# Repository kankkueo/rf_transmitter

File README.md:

# RF transmitter

## Contributors

### [Elmo Kankkunen](https://github.com/kankkueo)

### [Miikka Mäki](https://github.com/mimimaki)

### [Visa Kurvi](https://github.com/visakurvi)

## Description

The project is very low power and thus legal, but be aware of your local laws and regulations!

RF transmitter project for Aalto university course Elektroniikkapaja. The transmitter consists of a digital and analog circuits. The digital circuit has an ATMEGA328 microcontroller, which controls a digital potentiometer. This potentiometer sets the voltage level of an MAX2606 VCO input. This is how the transmitter frequency is controlled. Audio from a microphone is then modulated to this FM-signal. 

## Screenshots

## SDR++ captured demo

[Demo video](https://drive.google.com/file/d/1DeKwweD5EkPlx5URQ9tuIAPdqHnWOvnQ/view?usp=sharing/)

## License

MIT License

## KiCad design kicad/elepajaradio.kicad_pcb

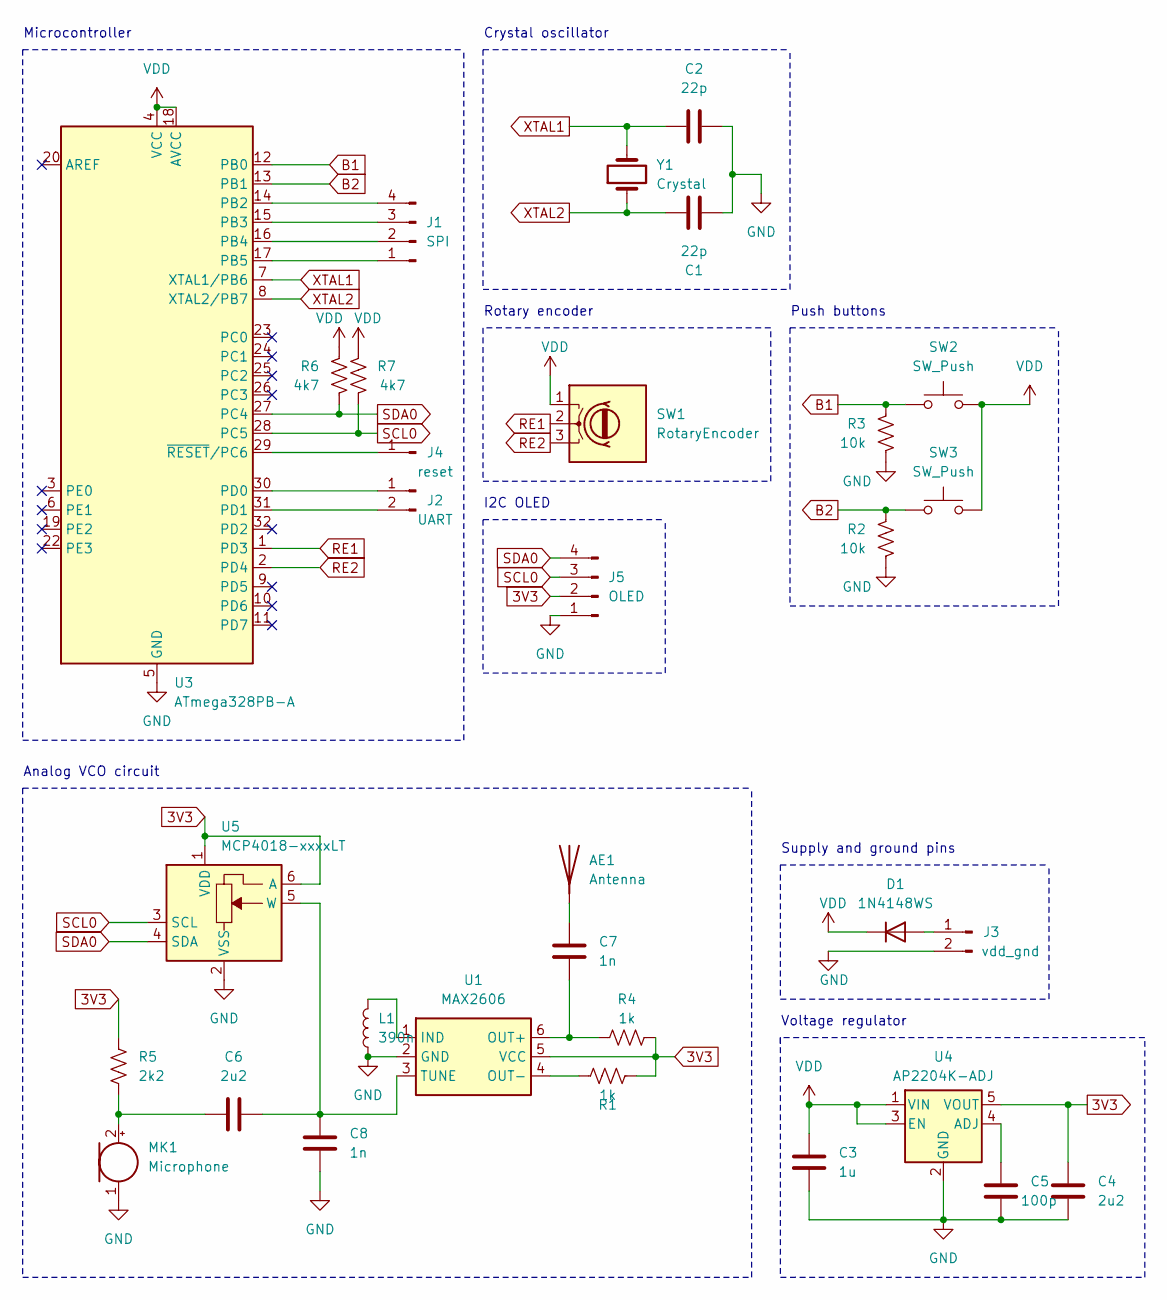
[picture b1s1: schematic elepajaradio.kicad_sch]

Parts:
AE1: Antenna; SMA_Amphenol_901-143_Horizontal
C1, C2: 22p; C_0603_1608Metric
C3: 1u; C_0603_1608Metric
C4, C6: 2u2; C_0603_1608Metric
C5: 100p; C_0603_1608Metric
C7, C8: 1n; C_0603_1608Metric
D1: 1N4148WS; D_SOD-323
J1: SPI; PinHeader_1x04_P2.54mm_Vertical
J2: UART; PinHeader_1x02_P2.54mm_Vertical
J3: vdd_gnd; PinHeader_1x02_P2.54mm_Vertical
J4: reset; PinHeader_1x01_P2.54mm_Vertical
J5: OLED; PinHeader_1x04_P2.54mm_Vertical
L1: 390n; L_0603_1608Metric
MK1: Microphone; PinHeader_1x02_P2.54mm_Vertical
R1, R4: 1k; R_0603_1608Metric
R2, R3: 10k; R_0603_1608Metric
R5: 2k2; R_0603_1608Metric
R6, R7: 4k7; R_0603_1608Metric
SW1: RotaryEncoder; PinHeader_1x03_P2.54mm_Vertical
SW2, SW3: SW_Push; PinHeader_1x02_P2.54mm_Vertical
U1: MAX2606; SOT-23-6
U3: ATmega328PB-A; TQFP-32_7x7mm_P0.8mm
U4: AP2204K-ADJ; SOT-23-5
U5: MCP4018-xxxxLT; SOT-363_SC-70-6
Y1: Crystal; Crystal_HC18-U_Vertical

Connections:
3V3: C4.1, J5.2, R1.1, R4.1, R5.2, U1.5 (VCC), U4.5 (VOUT), U5.1 (VDD), U5.6 (A)
B1: R3.2, SW2.1, U3.12 (PB0)
B2: R2.2, SW3.1, U3.13 (PB1)
GND: AE1.2, C1.2, C2.2, C3.2, C4.2, C5.2, C8.2, J3.2, J5.1, L1.1, MK1.1 (-), R2.1, R3.1, U1.2 (GND), U3.5 (GND), U3.21 (GND), U4.2 (GND), U5.2 (VSS)
unnamed: AE1.1 (A), C7.1
unnamed: D1.2 (A), J3.1
unnamed: J1.1, U3.17 (PB5)
unnamed: J1.2, U3.16 (PB4)
unnamed: J1.3, U3.15 (PB3)
unnamed: J1.4, U3.14 (PB2)
unnamed: J2.1, U3.30 (PD0)
unnamed: J2.2, U3.31 (PD1)
unnamed: J4.1, U3.29 (~RESET/PC6)
unnamed: C6.1, MK1.2 (+), R5.1
unnamed: L1.2, U1.1 (IND)
unnamed: C7.2, R4.2, U1.6 (OUT+)
unnamed: R1.2, U1.4 (OUT-)
unnamed: C6.2, C8.1, U1.3 (TUNE), U5.5 (W)
unnamed: C5.1, U4.4 (ADJ)
RE1: SW1.2, U3.1 (PD3)
RE2: SW1.3, U3.2 (PD4)
SCL0: J5.3, R7.1, U3.28 (PC5), U5.3 (SCL)
SDA0: J5.4, R6.1, U3.27 (PC4), U5.4 (SDA)
VDD: C3.1, D1.1 (K), R6.2, R7.2, SW1.1, SW2.2, SW3.2, U3.4 (VCC), U3.18 (AVCC), U4.1 (VIN), U4.3 (EN)
XTAL1: C2.1, U3.7 (XTAL1/PB6), Y1.2
XTAL2: C1.1, U3.8 (XTAL2/PB7), Y1.1

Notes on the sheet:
Microcontroller
Analog VCO circuit
Crystal oscillator
I2C OLED
Push buttons
Supply and ground pins
Rotary encoder
Voltage regulator

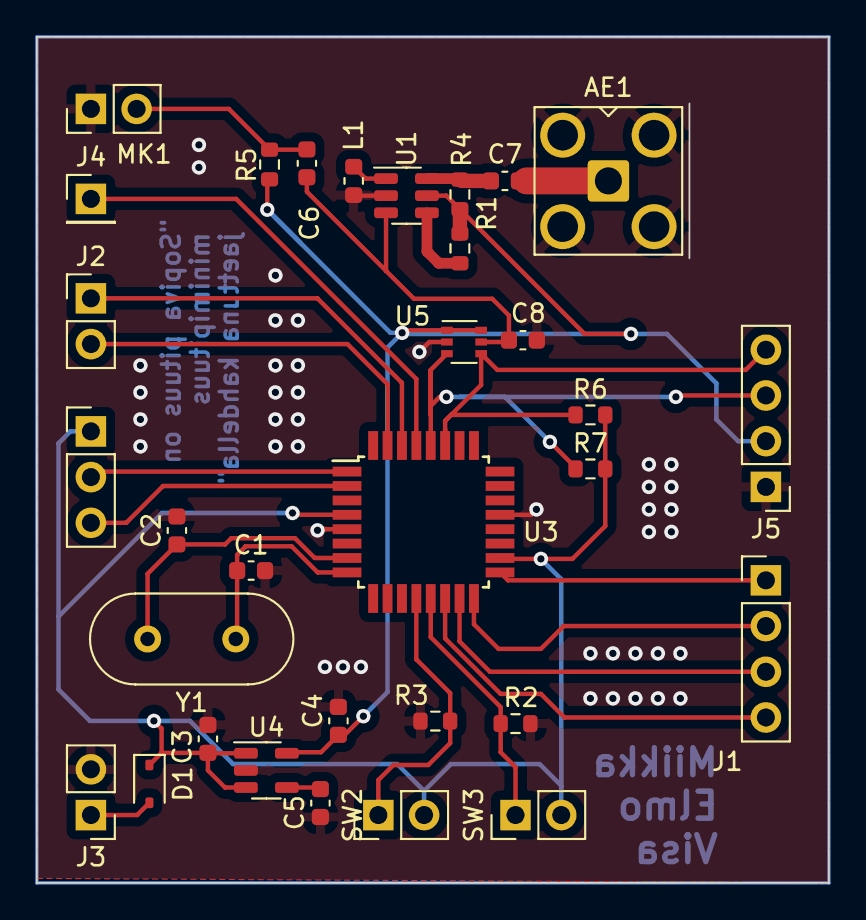
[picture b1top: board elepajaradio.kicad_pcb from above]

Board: 2 copper layers, 44.0 x 47.0 mm, 32 parts (0 on the bottom side), 26 nets.

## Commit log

2023-10-17 Add readme
2023-10-23 lisätään kicad projekti
2023-10-26 kicad update
2023-10-26 adding doc file and spice simulation file
2023-10-30 new circuit added
2023-11-07 initial pcb design and adding antenna connector
2023-11-09 resized transmission line for pcb
2023-11-09 sized transmission line v2
2023-11-09 adding PCB gbr and drl files
2023-11-24 initial C program
2023-11-25 fixes on new branch for 3v3 node
2023-11-26 fixing vco output nodes
2023-11-26 schematic updates for documentation
2023-11-28 makefile
2023-11-28 adding 3D model
2023-11-28 updates for second order
2023-11-28 Edited port values
2023-12-02 kicad gitignore
2023-12-04 removing unnecessary files
2023-12-04 making documentation in README
2023-12-04 figures for documentation
2023-12-04 fixing video extension
2023-12-04 fixing readme
2023-12-04 cleaning git
2023-12-07 combining i2cmaster.c and main.c
2023-12-08 edited main
2023-12-08 new i2c lib
2023-12-10 added temporary .ino testing code
2023-12-13 Working potentiometer
2023-12-13 deleted ino files
2023-12-13 deleted binary files
2023-12-14 Display frequency mapping
2023-12-14 Added software readme
2023-12-14 remoced old lib
2023-12-14 pull-up resistors and diode added
2023-12-14 fix readme this time maybe
2023-12-14 updating figures
2023-12-14 fixing text
2023-12-14 pcb fix
2023-12-14 fixes
